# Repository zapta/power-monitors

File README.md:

POWER PLAY
==========

POWER PLAY are Arduino based smart power monitors that are used to measure and optimize the power consumption of battery operated devices such as smart phones. 

Following is a description of the POWER PLAY models.

POWER PLAY 3.8V
---------------

This model provides the most accurate results but requires modifying the tested device. The POWER PLAY 3.8V outputs regulated 3.8 volts are simulates the power provided by a single cell Li-Ion battery cell. It requires disconnecting the battery from the tested device and hooking the output of the POWER PLAY 3.8V instead.

This model has 1.3" OLED display and on board analysis firmware such that it can be operated standalone. In addition is has a FTDI/USB output port that can be used to log the raw data on an attached computer and use it latter for additional analysis.

POWER PLAY 3.8V
---------------

This model is identical to the POWER PLAY 3.8V except that it does not have the 3.8V regulator and instead it outputs a pass through 5V. It is intended to be used with unmodified test device by connecting the power to the charger input of the test device and measuring the current fluctuations after the internal battery is fully charged. This method provides less accurate results than the POWER PLAY 3.8V (with the battery removed) but is easier to use since it does not require modifying the test devices.

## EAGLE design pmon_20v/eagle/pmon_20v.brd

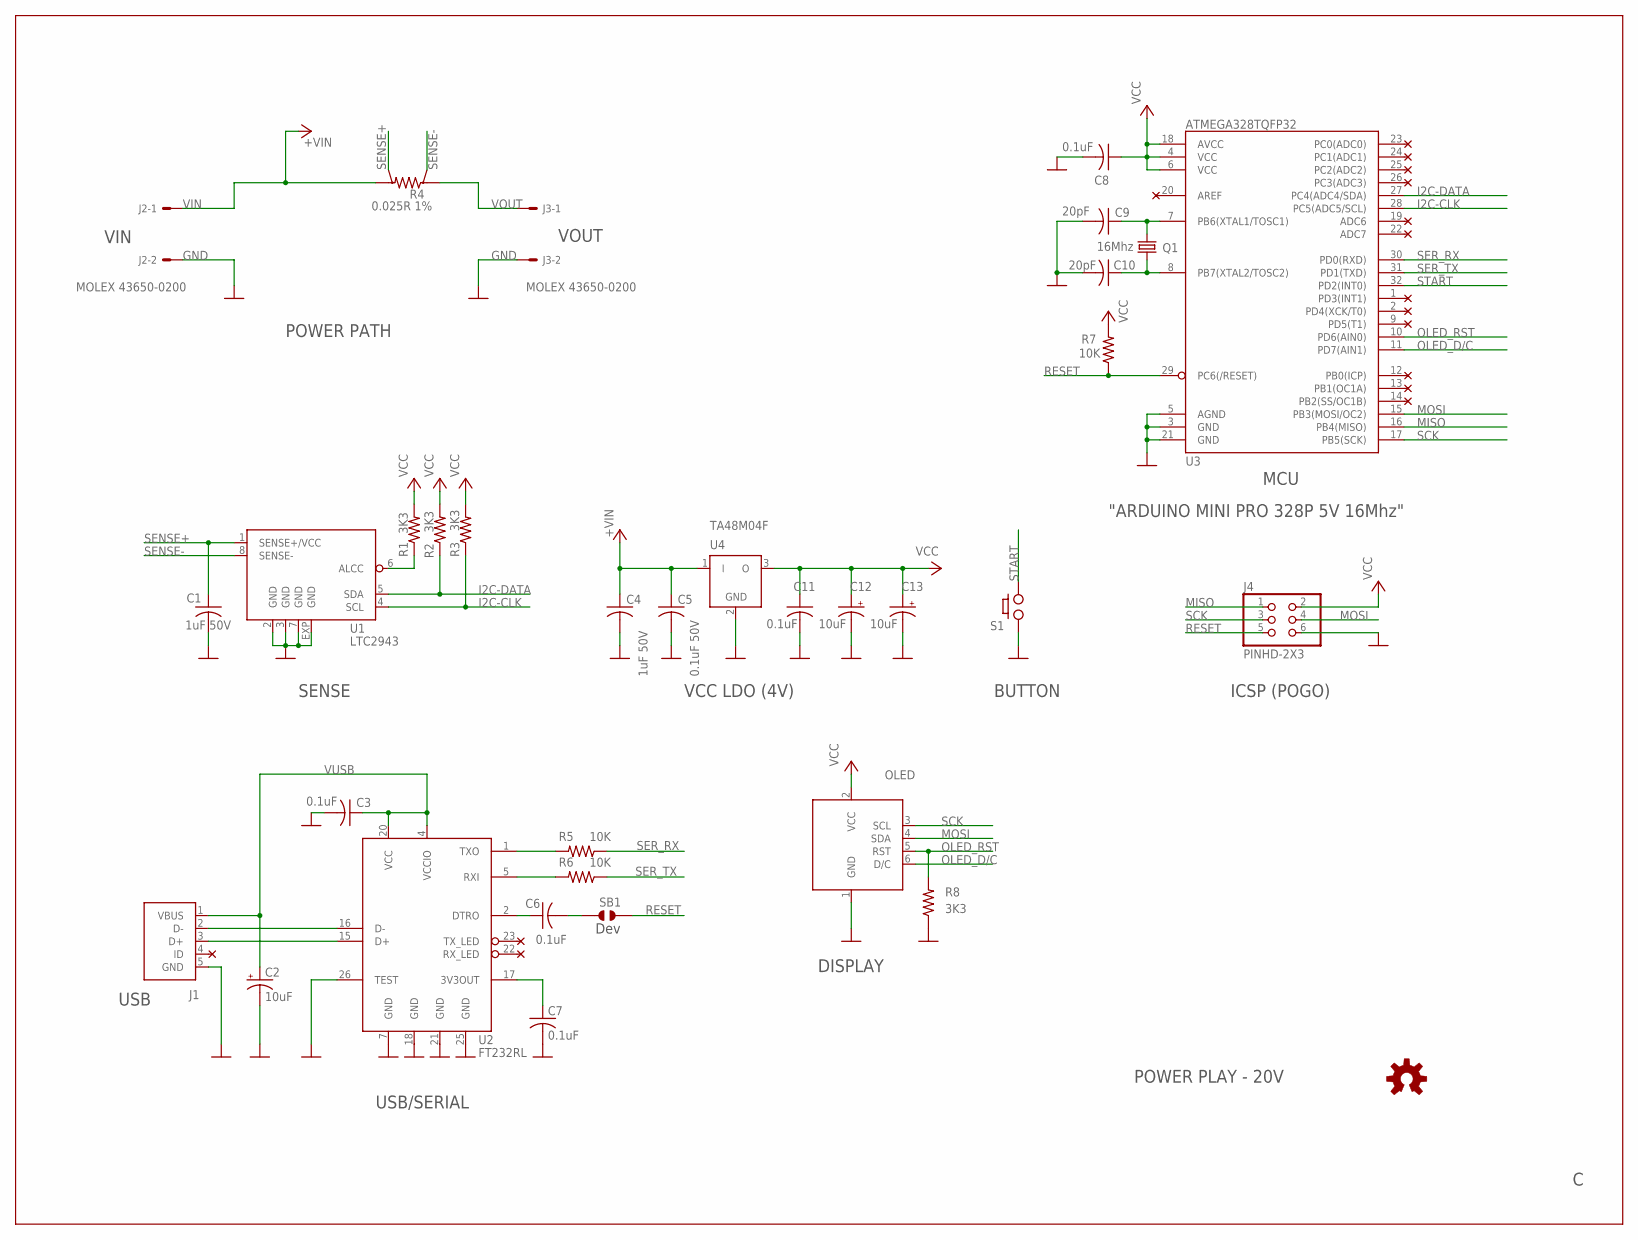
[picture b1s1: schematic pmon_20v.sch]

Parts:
C1, C4: 1uF 50V; C0603
C2, C12, C13: 10uF; A/3216-18R
C3, C6, C7, C8, C11: 0.1uF; C0603
C5: 0.1uF 50V; C0603
C9, C10: 20pF; C0603
J1: USB; USB-MICRO-ZX62RD-AB-5P8
J2, J3: MOLEX 43650-0200; POWER_CON
J4: PINHD-2X3; 2X03
OLED: OLED
Q1: 16Mhz; CRYSTAL-CTS406
R1, R2, R3, R8: 3K3; R0603
R4: 0.025R 1%; KELVIN-6432
R5, R6, R7: 10K; R0603
S1: PUSH_BUTTON; TLE1105
SB1: JUMPER_SOLDER_1X2
U1: LTC2943; DFN8-3X3
U2: FT232RL; SSOP28DB
U3: ATMEGA328TQFP32; TQFP32-08
U4: TA48M04F; DPACK
U$28: OSH

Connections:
GND: C1.2, C2.-, C3.2, C4.2, C5.2, C7.2, C8.2, C9.2, C10.2, C11.2, C12.-, C13.-, J1.5 (GND), J2.2, J3.2, J4.6, OLED.1 (GND), R8.1, S1.A (1), U1.2 (GND), U1.3 (GND), U1.7 (GND), U1.EXP (GND), U2.7 (GND), U2.18 (GND), U2.21 (GND), U2.25 (GND), U2.26 (TEST), U3.3 (GND), U3.5 (AGND), U3.21 (GND), U4.2 (GND)
I2C-CLK: R3.1, U1.4 (SCL), U3.28 (PC5(ADC5/SCL))
I2C-DATA: R2.1, U1.5 (SDA), U3.27 (PC4(ADC4/SDA))
MISO: J4.1, U3.16 (PB4(MISO))
MOSI: J4.4, OLED.4 (SDA), U3.15 (PB3(MOSI/OC2))
unnamed: R1.1, U1.6 (ALCC)
unnamed: C9.1, Q1.1, U3.7 (PB6(XTAL1/TOSC1))
unnamed: R5.2, U2.1 (TXO)
unnamed: C10.1, Q1.3 (2), U3.8 (PB7(XTAL2/TOSC2))
unnamed: R6.2, U2.5 (RXI)
unnamed: J1.3 (D+), U2.15 (D+)
unnamed: C6.1, U2.2 (DTRO)
unnamed: C6.2, SB1.1
unnamed: J1.2 (D-), U2.16 (D-)
unnamed: C7.1, U2.17 (3V3OUT)
OLED_D/C: OLED.6 (D/C), U3.11 (PD7(AIN1))
OLED_RST: OLED.5 (RST), R8.2, U3.10 (PD6(AIN0))
RESET: J4.5, R7.1, SB1.2, U3.29 (PC6(/RESET))
SCK: J4.3, OLED.3 (SCL), U3.17 (PB5(SCK))
SENSE+: C1.1, R4.V2, U1.1 (SENSE+/VCC)
SENSE-: R4.V1, U1.8 (SENSE-)
SER_RX: R5.1, U3.30 (PD0(RXD))
SER_TX: R6.1, U3.31 (PD1(TXD))
START: S1.B (2), U3.32 (PD2(INT0))
VCC: C8.1, C11.1, C12.+, C13.+, J4.2, OLED.2 (VCC), R1.2, R2.2, R3.2, R7.2, U3.4 (VCC), U3.6 (VCC), U3.18 (AVCC), U4.3 (O)
VIN: C4.1, C5.1, J2.1, R4.I2, U4.1 (I)
VOUT: J3.1, R4.I1
VUSB: C2.+, C3.1, J1.1 (VBUS), U2.4 (VCCIO), U2.20 (VCC)

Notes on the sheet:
USB/SERIAL
ICSP (POGO)
MCU
POWER PLAY - 20V
SENSE
POWER PATH
VIN
USB
VOUT
"ARDUINO MINI PRO 328P 5V 16Mhz"
BUTTON
DISPLAY
Dev
VCC LDO (4V)

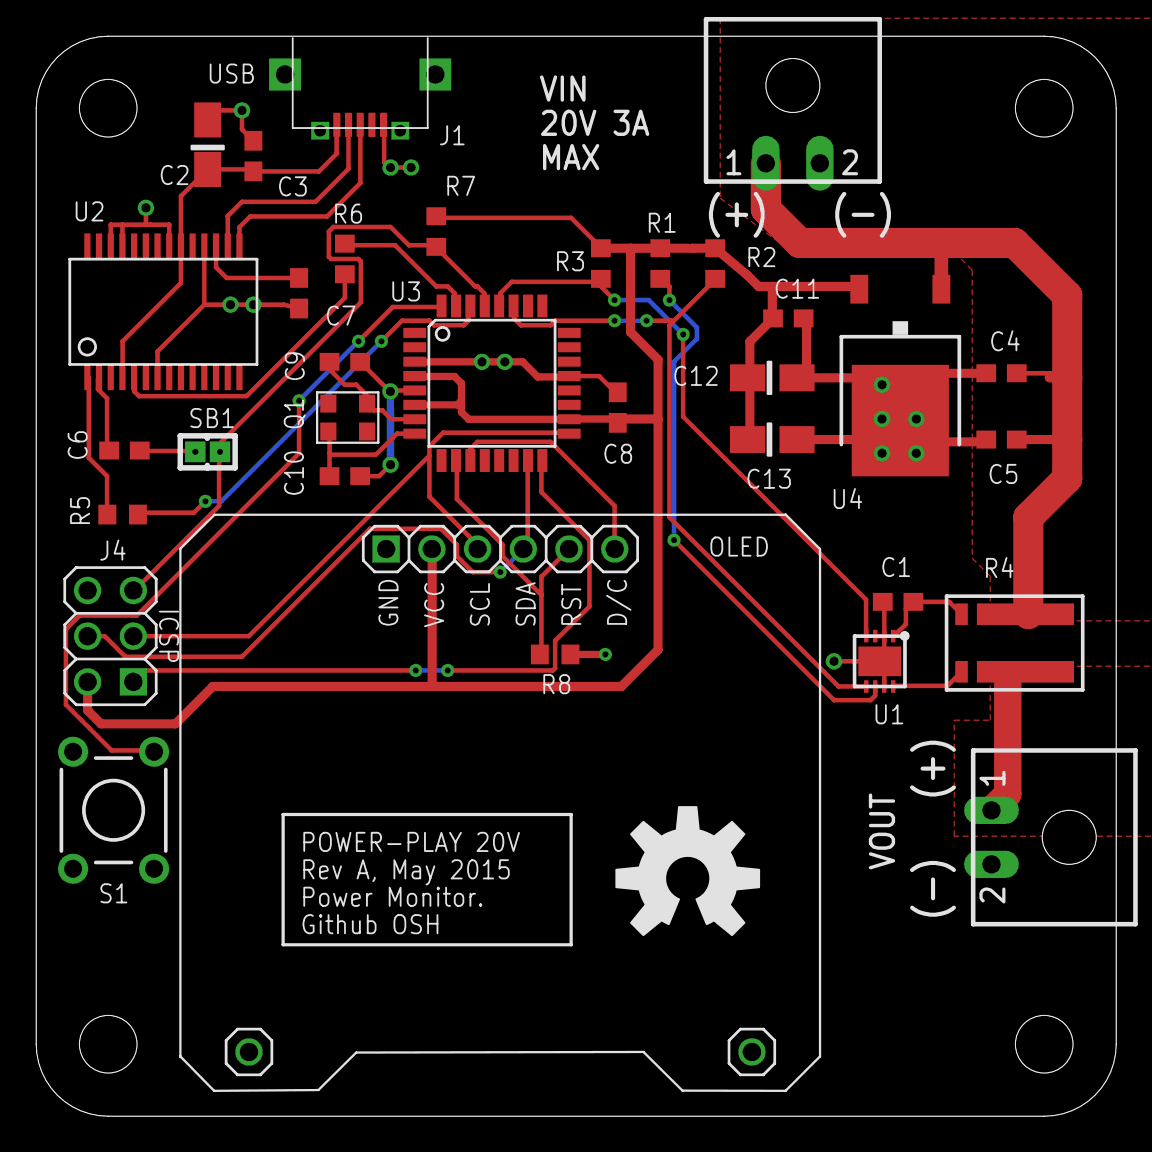
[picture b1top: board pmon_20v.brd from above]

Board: 2 copper layers, 60.0 x 60.0 mm, 34 parts (0 on the bottom side), 28 nets.

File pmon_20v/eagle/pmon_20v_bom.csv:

Quantity,Digi-Key Part Number,Description,Package,Manufacturer Name,Manufacturer Part Number,Part Numbers,Comments1,FC4L64R025FERCT-ND,0.025 ohm 1% 2W Kelvin,SMT 2512,Ohmite,FC4L64R025FER,R4,4,311-3.30KHRCT-ND,3.3K 5% 1/10W,SMT 0603,Yageo,RC0603JR-073K3L,R1  R2  R3  R8,Generic part3,311-10KGRCT-ND,10k 5% 1/10W,SMT 0603,Yageo,RC0603JR-0710KL,R5  R6  R7,Generic part2,311-1424-1-ND,20pF 50V 5%,SMT 0603,Yageo,CC0603JRNPO9BN200,C9  C10,Generic part5,311-1344-1-ND,0.1uf 10% 25V,SMT 0603,Yageo,CC0603KRX7R9BB104,C3  C5  C6  C8 C11,Generic part. May need to reduce C7 if interferes with ICSP reset (e.g. to 0.01)1,587-2400-1-ND,1uF 50V 10%,SMT 6030,Taiyo Uden,UMK107BJ105KA-T,C4,Generic part2,399-3684-1-ND,10uF 10%  16V,SMT 1206,Kemet,T491A106K010AT,C12  C13,Generic part1,CTX732CT-ND,16Mhz Crystal 20pf,4-SMD 3.20mm x 2.50mm,CTS-Frequency Control,403C11E16M00000,Q1,CTS 403 Series  20pF.1,ATMEGA328P-AURCT-ND,ATMEGA328P,TQFP32,Atmel,ATMEGA328P-AUR,U3,Atmel AVR328P1,768-1007-1-ND,FT232RL,SSOP28,FTDI,FT232RL-REEL,U2,1,LTC2943CDD#PBF-ND,LTC2943,DFN8,Liner Technology,LTC2943CDD#PBF,U1,Adjustable LDO 3A.1,TA48M04F(T6L1SNQ)CT-ND ,LDO 29V in 4V out,DPAK 2 + tab,Toshiba,"TA48M04F(T6L1,SNQ)",U4,Fixed LDO 4.0V. High input voltage1,P12197S-ND,Push button,,Panasonic Electronic Components,EVQ-PAG09K,S1,Panasonic EVQ-PAG09K2,S1011E-36-ND,"1 position  0.1""  straight",,Sullins Connector Solutions,PBC36SAAN,OLED mechanical support.,Generic part. Height above board should be at most 8.5mm. The part number here is for a 36 position breakable strip so it can be used for multiple boards.1,H11611CT-ND,Micro USB 'reversed' connector,,Hirose Electric Co Ltd,ZX62RD-AB-5P8,J1,Hirose ZX62RD-AB-5P8.  Make sure it is a 'reversed' connector  otherwise the signals will be in reversed order.2,WM1860-ND,PCB conn 2wire right angle,,Molex Inc,436500200,J2  J3,2,WM1845-ND,Conn header 2 wire,,Molex Inc,436450200,,4,WM2776CT-ND,Conn header contact female,,Molex Inc,430300003,,4,335-1156-ND,M3x6mm  pan head  philips machine screw,,APM Hexseal,RM3X6MM 2701,,Top cover screws4,335-1148-ND,M3x10mm  pan head  philips machine screw,,APM Hexseal,RM3X10MM 2701,,Bottom cover screws4,952-1515-ND,M3x6mm  round  threaded  female/female metal standoff,,Harwin,R30-5000602,,Top cover standoff4,952-1526-ND,M3x3mm round  non threaded nylon or metal spacer,,Harwin,R30-6700394,,Bottom cover spacer1,N/A,"Heltec 1.3"" SPI 128X64 OLED WHITE monochrome display with RST pin.",,Heltec,,OLED,Must have SSD1306 controller and these 6 pins: GND  VCC  SCL  SDA  RST  D/C (picture here  http://i.imgur.com/y3cWazS.jpg).  Manufacturer is http://www.heltec.cn. Heltec also similar blue models (with sh1063 controller) and 'new' models with different 6 pins (VCC and GND swapped  no RST pin)  these two models are incompatible with the current POWER PLAY design.1,N/A,PCB,,,,,Order the PCB from your favorite PCB manufacturer (2 layers  60x60mm).  Make sure to order a SMD stencil  preferably 5mil stainless steal but even a 5 mil stencil from oshstencils.com should work.1,N/A,Top cover,,,,,"Laser cut fluorescent green 1/8"" acryilic."1,N/A,Bottom Cover,,,,,"Laser cut fluorescent green 1/8"" acryilic."

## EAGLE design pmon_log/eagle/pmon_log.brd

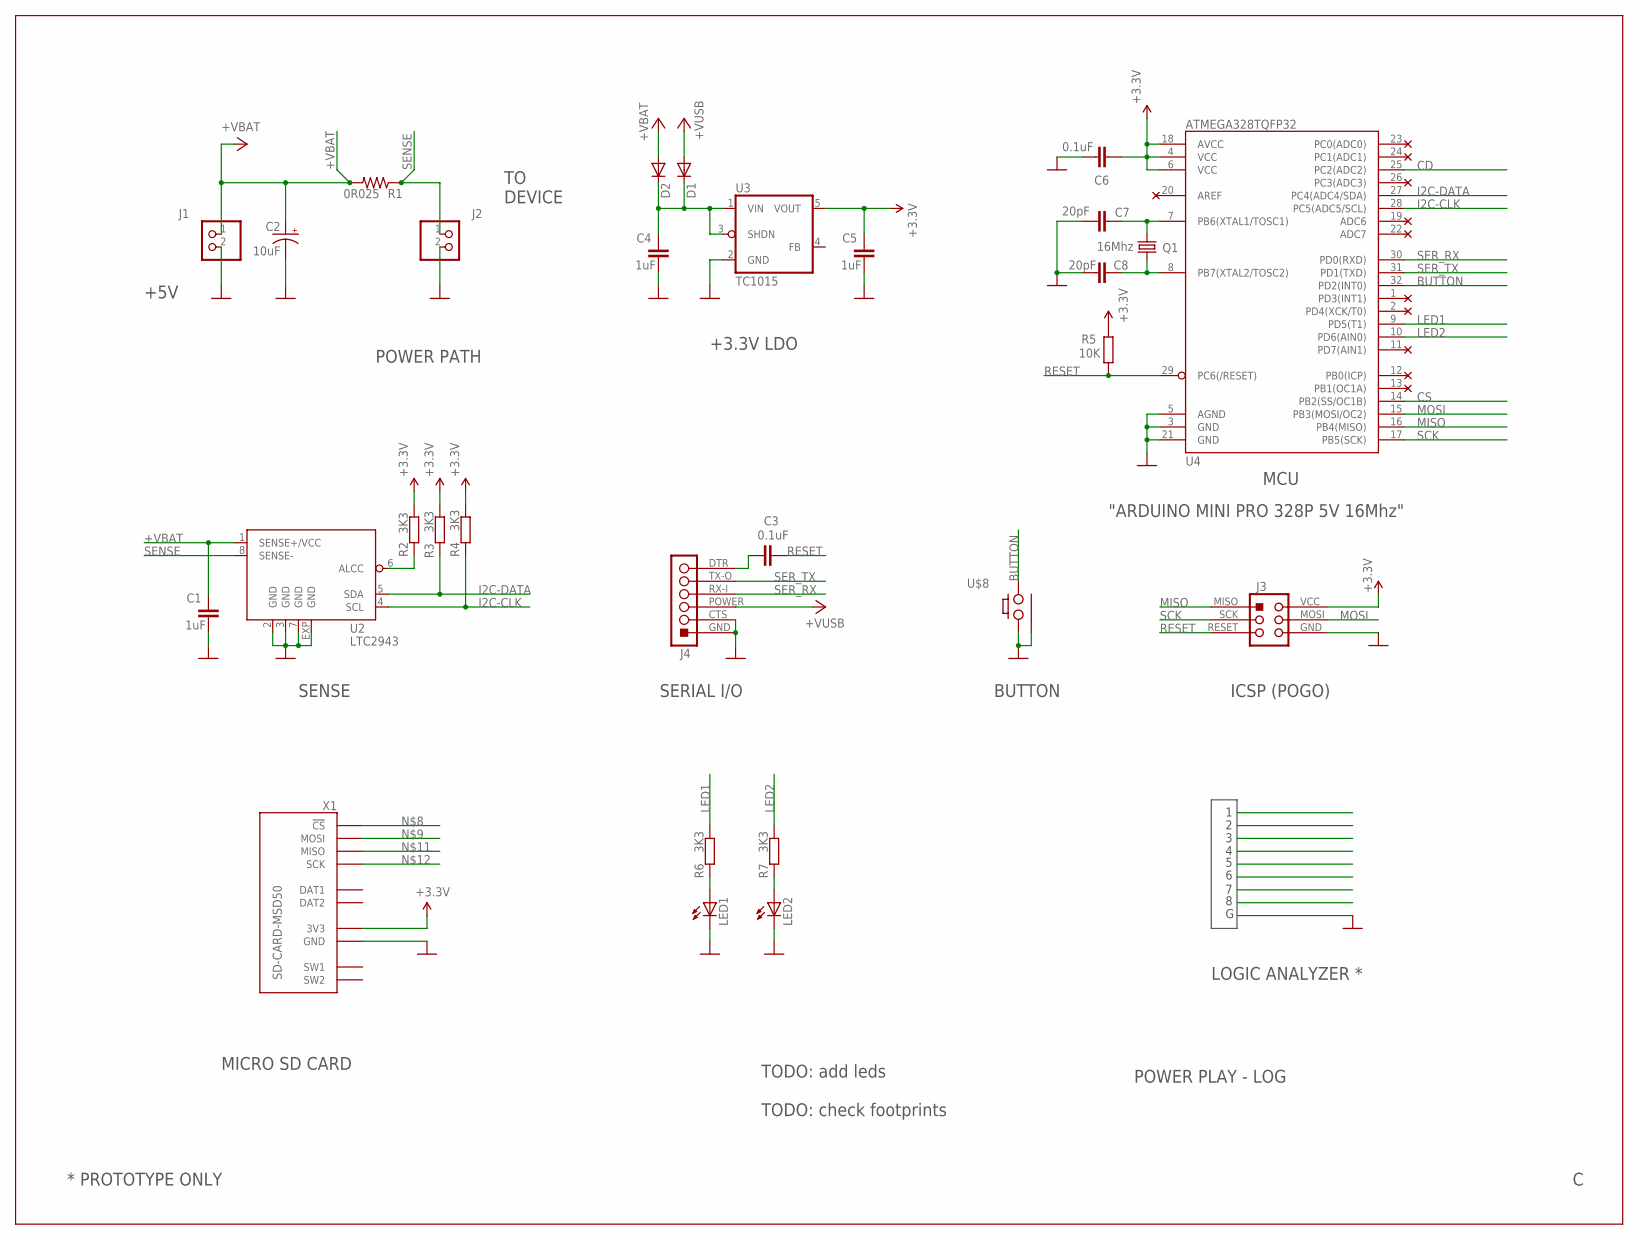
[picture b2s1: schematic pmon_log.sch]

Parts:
C1, C4, C5: 1uF; C0402K
C2: 10uF; A/3216-18R
C3, C6: 0.1uF; C0402K
C7, C8: 20pF; C0402K
D1, D2: DIODE-SC79_INFINEON; SC79_INFINEON
J1, J2: PINHD-1X2; 1X02
J3: ICSP
J4: SERIAL_HEADER
LED1, LED2: LEDCHIPLED_0603; CHIPLED_0603
Q1: 16Mhz; CRYSTAL-CTS406
R1: 0R025; R0603
R2, R3, R4, R6, R7: 3K3; R0402
R5: 10K; R0402
U2: LTC2943; DFN8-3X3
U3: TC1015; SOT25
U4: ATMEGA328TQFP32; TQFP32-08
U$8: PUSH_BUTTON_GND
X1: SD-CARD-MSD50; SD_5031821853

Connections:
+3.3V: X1.VCC (3V3)
+4V: C5.1, C6.1, J3.VCC, R2.2, R3.2, R4.2, R5.2, U3.5 (VOUT), U4.4 (VCC), U4.6 (VCC), U4.18 (AVCC)
+USB: D1.A, J4.POWER (3)
+VBAT: C1.1, C2.+, D2.A, J1.1, R1.2, U2.1 (SENSE+/VCC)
BUTTON: U4.32 (PD2(INT0)), U$8.HOLE1 (2)
CD: U4.25 (PC2(ADC2))
CS: U4.14 (PB2(SS/OC1B))
GND: C1.2, C2.-, C4.2, C5.2, C6.2, C7.2, C8.2, J1.2, J2.2, J3.GND, J4.CTS (2), J4.GND (1), LED1.C, LED2.C, U2.2 (GND), U2.3 (GND), U2.7 (GND), U2.EXP (GND), U3.2 (GND), U4.3 (GND), U4.5 (AGND), U4.21 (GND), U$8.A1 (1), U$8.GND, X1.GND
I2C-CLK: R4.1, U2.4 (SCL), U4.28 (PC5(ADC5/SCL))
I2C-DATA: R3.1, U2.5 (SDA), U4.27 (PC4(ADC4/SDA))
LED1: R6.2, U4.9 (PD5(T1))
LED2: R7.2, U4.10 (PD6(AIN0))
MISO: J3.MISO, U4.16 (PB4(MISO))
MOSI: J3.MOSI, U4.15 (PB3(MOSI/OC2))
unnamed: R2.1, U2.6 (ALCC)
unnamed: C7.1, Q1.1, U4.7 (PB6(XTAL1/TOSC1))
unnamed: C4.1, D1.C, D2.C, U3.1 (VIN), U3.3 (SHDN)
unnamed: LED1.A, R6.1
unnamed: LED2.A, R7.1
unnamed: C8.1, Q1.3 (2), U4.8 (PB7(XTAL2/TOSC2))
unnamed: C3.2, J4.DTR (6)
RESET: C3.1, J3.RESET, R5.1, U4.29 (PC6(/RESET))
SCK: J3.SCK, U4.17 (PB5(SCK))
SENSE: J2.1, R1.1, U2.8 (SENSE-)
SER_RX: J4.RX-I (4), U4.30 (PD0(RXD))
SER_TX: J4.TX-O (5), U4.31 (PD1(TXD))

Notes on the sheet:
ICSP (POGO)
MCU
POWER PLAY - LOG
SENSE
POWER PATH
+5V
LOGIC ANALYZER *
TO DEVICE
* PROTOTYPE ONLY
"ARDUINO MINI PRO 328P 5V 16Mhz"
BUTTON
+3.3V LDO
TODO: add leds
TODO: check footprints
SERIAL I/O
MICRO SD CARD

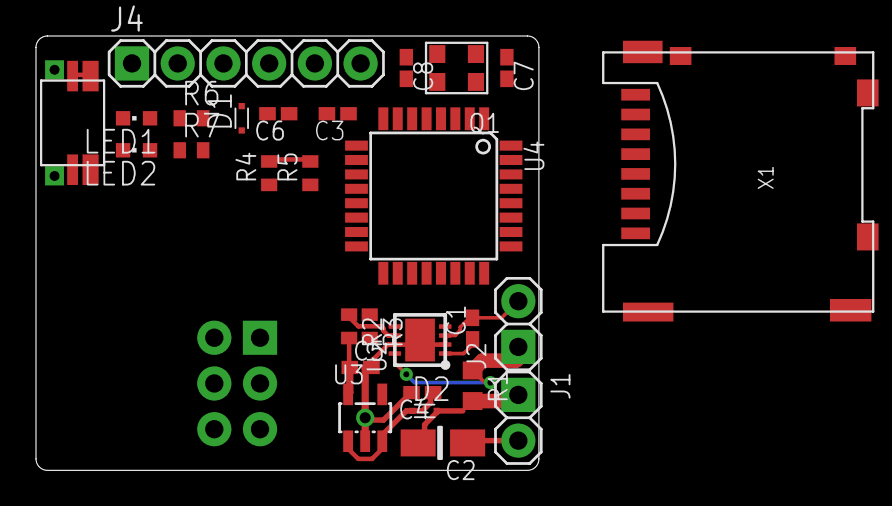
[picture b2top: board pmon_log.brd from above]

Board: 2 copper layers, 27.9 x 24.1 mm, 29 parts (1 on the bottom side), 23 nets.

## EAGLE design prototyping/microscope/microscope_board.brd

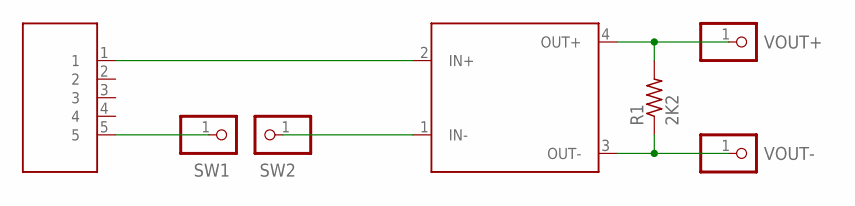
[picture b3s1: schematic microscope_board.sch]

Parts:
R1: 2K2; R0805
SW1, SW2: PINHD-1X1; 1X01
U$1: DC_DC
U$2: USB_CONNECTOR
VOUT+: PINHD-1X1; 1X01
VOUT-: PINHD-1X1; 1X01

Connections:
unnamed: R1.2, U$1.4 (OUT+), VOUT+.1
unnamed: R1.1, U$1.3 (OUT-), VOUT-.1
unnamed: U$1.2 (IN+), U$2.1
unnamed: SW1.1, U$2.5
unnamed: SW2.1, U$1.1 (IN-)

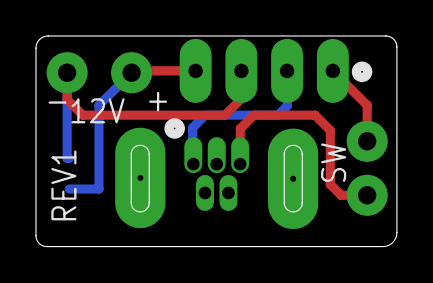
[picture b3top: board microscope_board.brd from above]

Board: 2 copper layers, 20.1 x 11.7 mm, 7 parts (1 on the bottom side), 5 nets.

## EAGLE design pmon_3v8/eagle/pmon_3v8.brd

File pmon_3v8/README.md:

POWER PLAY 3.8V
===============

## OVERVIEW
POWER PLAY 3V8 is an Arduino based measurement tool that is used to measure the power consumption of mobile devices under different conditions and software versions. It provides 3.8V 2A DC power that simulates a single cell Li-ion battery and is connected to the device **instead of the battery**. The POWER PLAY 3V8 analyzes the current pattern consumed by the device and provides aggregated data on an integral a 1.3" OLED display. It also output the data to a USB/Serial port so it can be logged by a computer for further analysis. The computer based logging is optional and in most cases not consumed since the POWER PLAY 3V8 provides the key results on the display in real time (e.g. the average current consumption over the measurement period).

**WARNING using the POWER PLAY 3.8V required modified devices with batteries removed. This modification should be done by qualified persons only due to the risk of fire, personal injury and even death. The POWER PLAY 3V8 information is provided here as-is and you must consult a qualified person before using it in any way. NEVER operate the POWER PLAY 3V8 with the battery connected to the device under test.**

1. +5V power input micro USB connector. This connector should be connected to a standard 5V charger and is used to power the POWER PLAY 3V8 and the device under test. It is important to use a charger that can provide sufficient current even during peak current consumption by the device under test. When testing a typical smart phone, powering the POWER PLAY 3V8 from a USB port or a small 1A charger typically result in insufficient current and unstable operation.

2. Power output connection to the device. This is a 3 pin standard servo connector (JR and Hitec style) with ground at the center pin and 3.8V DC (typical) at the two end pins (it's sufficient to use only one of them). This output voltage is adjustable (see below) and is connected to the device instead of the battery, emulating a single cell Lithium-ion battery.

3. USB connector. Using this connector is optional. It allows to log the raw data on an attached computer for later analysis. This connector implements a FTDI serial over USB port and can be access as a serial port on standard Mac OSX, Linux and Windows computers without additional drivers. The emulated serial port is 115.2kbs, 8 data bit, no parity and the data is in ASCII text format.

4. Display. This is a 1.3" monochrome OLED display that shows the analysis results. The display supports multiple pages with different data items.

5. Operation button. A short click switch the displayed data page and a long press (~4 seconds) resets the analysis variables and starts a new analysis session. Holding this button pressed while powering the POWER PLAY 3V8 activates the test screen (for post manufacturing tests).

6. This is a multi turn trim potentiometer that allows to adjust the output voltage in the range 3.6V - 4.2V. It is accessible from the side of the POWER PLAY 3V8 and requires a small flat screwdriver.

7. Auto Reset. This is a solder jumper on the PCB that controls the the USB auto reset feature. When shorted, establishing a new connection via the USB connector resets the POWER PLAY 3V8. This is useful when developing firmware for the POWER PLAY 3V8 using the Arduino IDE. If the auto reset is not desired (e.g. in order to have analysis sessions non interrupted by connecting the USB port), the short should be disconnected with a solder iron (after removing the 4 top screws and top cover).

TODO: add an overall picture with annotation for connectors, display, button and trim pot.

## FUNCTIONAL BLOCK DIAGRAM

* **Voltage regulator** - a 5V to 3.8v low dropout (LDO) voltage regulator. The output voltage (nominal 3.8V) can be set by the small multi turn potentiometer on the right hand of the device.
* **Shunt resistor** - this is a small (25 milliohms) 1% Kelvin resistor that is used to sample the current consumed the the device. The voltage drop on the shunt does not affect the output voltage of the POWER PLAY 3V8 because of the feedback loop between the output voltage and the LDO.
* **Coulomb counter** - this is an analog circuit that continuously integrate the current through the shunt resistor and generates a pulse ('tick') whenever the charge since the last tick reaches a predefined value. (charge is the integral of current over time and is measured in Ampere Hours). For more information read the LTC2943 datasheet at http://www.linear.com/product/LTC2943.
* **Charge counter** - this is a digital counter that counts the Coulomb counter ticks. It provides the long term current integration.
* **Analysis** - this is firmware that tracks the current patterns and computes real time summary data such as momentary current, accumulated charge, number of times device transitioned from standby to wake mode and so on.
* **Display** - a small 1.3" OLED display that display the analysis results. The display has several pages, each with different data items, that can be switched using the button.
* **Computer** - this is an optional computer that logs the data over a USB connection. In most cases, the results displayed on the OLED displayed are sufficient and the computer is not necessary. 

## CONNECTION DIAGRAM

Plug the +5V micro usb connector to a USB charger with sufficient current (e.g. 2A). Plug the modified device to the DEVICE connector. Optional: to log the data on a computer connect the USB port to a computer and run a logging program or script (the POWER PLAY 3V8 looks like a 115.2kbs FTDI serial over USB port).

## ANALYSIS

The POWER PLAY 3V8 performs the analysis by dividing the time into slots of 100ms each (10Hz). For each time slot the analysis firmware samples the number of charge ticks occurred in that time slot (partial ticks are rolled to the next time slots, avoiding integration errors) and tracks the total ticks and time in global analysis counters. These counters are reset when the analysis is reset by long pressing the button. These values are used to compute, report and display the following values among others:

* Charge in last time slot.
* Average current during last time slot.
* Last time slot classification (I < ~80ma ? 'standby' : 'wake').
* Total analysis time.
* Total analysis charge (AmpHour).
* Average current during the analysis period.
* Total times of 'wake' and 'standby' slots.
* Total charge in 'wake' and 'standby' slots.
* Number of transitions from a 'standby' to 'wake' time slot.

The most important value from the above list is the average current during the analysis since it is inversely proportional to the expected battery life (for a given battery capacity).

Note: the analysis also samples and reports the momentary voltage level at each slot but in general it assumes that the voltage is fixed and thus does not track power (Watt) or energy (Watt Hour).

## OPERATION

Operating the POWER PLAY 3V8 is very simple. Connect the POWER PLAY 3V8 to a 5V 2A charger and the device under test as described above, reset the analysis by long pressing the button (~4 seconds) and let the device operate under the desired conditions. The analysis is done is real time and the results are shown on the display. Click the button to switch between display pages to see the desired values. 

IMPORTANT: the charger must be able to provide the peak current of the device under test. Make sure to have a brand name charger with sufficient power capabilities (e.g. 2A or larger). If the charger cannot provides the peak current, the device will turn off occasionally. 

## LOG FORMAT
POWER PLAY output raw data for logging and offline analysis via the USB port. When connecting to a Linux, Mac OSC or Windows 
computer, the POWER PLAY appears as a serial port without having to install any special driver (it uses the default FTDI driver).
The serial port parameters are 115,200 bps, 8 data bit, no parity and it provides text based data (with CR/LF line ending)
with one record every 100 milliseconds. Each record contains the values listed below with a single space separator between
them.

```
8.200 0.131 0.000 0.163 0 8200 1 1
8.300 0.155 0.000 0.163 0 8300 1 1
8.400 0.131 0.000 0.163 0 8400 1 1
8.500 0.042 0.000 0.161 100 8400 1 0
8.600 0.018 0.000 0.159 200 8400 1 0
8.700 0.018 0.000 0.158 300 8400 1 0
8.800 0.012 0.000 0.156 400 8400 1 0
8.900 0.018 0.000 0.155 500 8400 1 0
9.000 0.030 0.000 0.153 600 8400 1 0
9.100 0.060 0.000 0.152 600 8500 2 1
9.200 0.042 0.000 0.151 700 8500 2 0
```

The fields of each log line are as follows

* **T** - Timestamp since the beginning of the analysis (long press the button) in milliseconds.
* **I** - Average current during the last 100ms time slot, in Amperes.
* **Q** - Total charge since the beginning of the analysis in Ampere/Hours.
* **Iavg** - Average current since the beginning of the analysis in millliamps.
* **Ts** - Total time since the beginning of the analysis of 100ms time slot that were classified as 'standby' (average current was lower than a predefined threshold.
* **Tw** - Total time since the beginning of the analysis of 100ms time slot that were classified as 'wake' (average current was higher than a predefined threshold. (this field is redundant since it is always equals T - Ts).
* **Nw** - number of transitions from a 'standby' (100ms) time slot to a 'wake' time slot. 
* **W** - a boolean flag that indicates if the last 100ms time slot was classified as 'wake' (value = 1) or as 'standby' (value = 0).

## INSTRUMENTING A DEVICE
The process of instrumenting a mobile device to be used with POWER PLAY 3.8V varies for each device and should be done only by qualified personal that understand the device and the hazards of dealing with rechargeable Li-Ion batteries (risk or fire, personal injury and death so **beware**). For that reason, it is in out of the scope of this document.

Following are the steps used to instrument one specific phone model (Nexus 5) that was used to test the POWER PLAY 3.8V. This is provided as general information only and not as a comprehensive guide. The procedure for other devices can be very different, some may require additional capacitors in parallel to the two wires, other can require special 'fake' batteries while others can be completely incompatible with POWER PLAY 3.8V.

1. Open the back cover (pry around)
2. Remove the black plastic cover above the battery (require removal of 6 small screws).
3. Carefully disconnect the battery connector and the large flex connector next to it.
4. Remove the battery (you need to pry below it, be careful not to damage the battery).
5. Place back the large flex cable.
6. Solder two wires to the points shown the in the picture below.
7. Put back the black cover and secure with the 6 screws.
8. Cut a small notch at the edge of the back cover to have clearance for the two wires.
9. Put back the black cover.
10. Solder the two wires to a 3 position HiTech/JR (but not Futaba) servo connector. Connect the center position to the (-) wires and one of the end positions to the (+) wire.

The Nexus 5 with cover and battery removed and two wires soldered.

A close up of the two connection points.

The phone with the black cover back in place and the wires secured with tape.

The exit point of the two wires.

## FIRMWARE DEVELOPMENT

POWER PLAY 3.8V is compatible with the Arduino IDE and its firmware is an Arduino sketch whose source code is available in this directory. Here are a few notes that will help you setup the development environment.

* You need to power the POWER PLAY 3.8V via its +5V connector in addition to connecting the USB port to the host computer with the Arduino IDE.
* The POWER PLAY 3.8V looks to the Arduino IDE as an Arduino Pro Mini 16Mhz 5V ATMEGA328 board. You need to select it in the Tool section of the IDE menu.
* You can use the IDE serial monitor facility to view output from the POWER PLAY 3.8V.
* The POWER PLAY 3.8V sketch uses the U8glib graphic library. You need to install it on your Arduino IDE before being to compile the POWER PLAY 3.8V sketch. To do so, follow the 'manual instructions' here https://code.google.com/p/u8glib/wiki/u8glib (using the IDE's library import function results in compilation errors).

## BUILDING POWER PLAY 3V8

Follow these steps to build your own POWER PLAY: 

* Purchase the electronic components listed in the Bill Of Material (BOM) file. Most components are available from common sources such as digikey.com. You can purchase the OLED display directly from heltec.cn or from retailers such as eBay sellers. Make sure to purchase a white SPI display with 6 pins that match the pins in the schema (these display use the SSD1306 controller).
* Order the printed circuit board (PCB). It is a 2 layers PCB with a Sick of Beige 60mm x 60mm form factor. Some vendors such as OSHPark.com accept Eagle .brd files directly. Others such as elecrow.com require you to generate gerber files using their custom Eagle .cam files.
* Order a SMD stencil (5mil or 0.125mm) for the PCB. For best results, use a metal stencil (e.g. from elecrow.com) rather than mylar.
(optional) Make the top and bottom laser cut covers. We got the best results with acrylic 1/8” fluoro blue or green. If you do not have access to a laser cutter, you can order online from services such as ponoko.com. 
* Print, pick-and-place and reflow the SMD components, including the two micro USB connectors (use solder paste, the stencil and the reflow method of your choice such as hot air station, hot plate or a toaster oven).
* Solder the through-hole components (two 1 pin OLED support posts, OLED display, push button, and 3 pin output header). Connecting the solder jumper SB1 is optional but recommended.
* Power the board via the +5V connector and use an ICSP programmer of your choice (e.g. Atmel ICSP MKII with pogo pins) to program the MCU  (see the script file icsp_program_all.sh for an example). Alternatively, you can program the MCU before soldering, using a universal programmer. This step programs the MCU fuses, the MCU Arduino bootloader, and the POWER PLAY firmware. 
* (optional) Assemble the top and bottom covers using the screws and spacers listed in the BOM. If not using the covers, you can use screws and nuts to have the PCB standing on 4 legs.

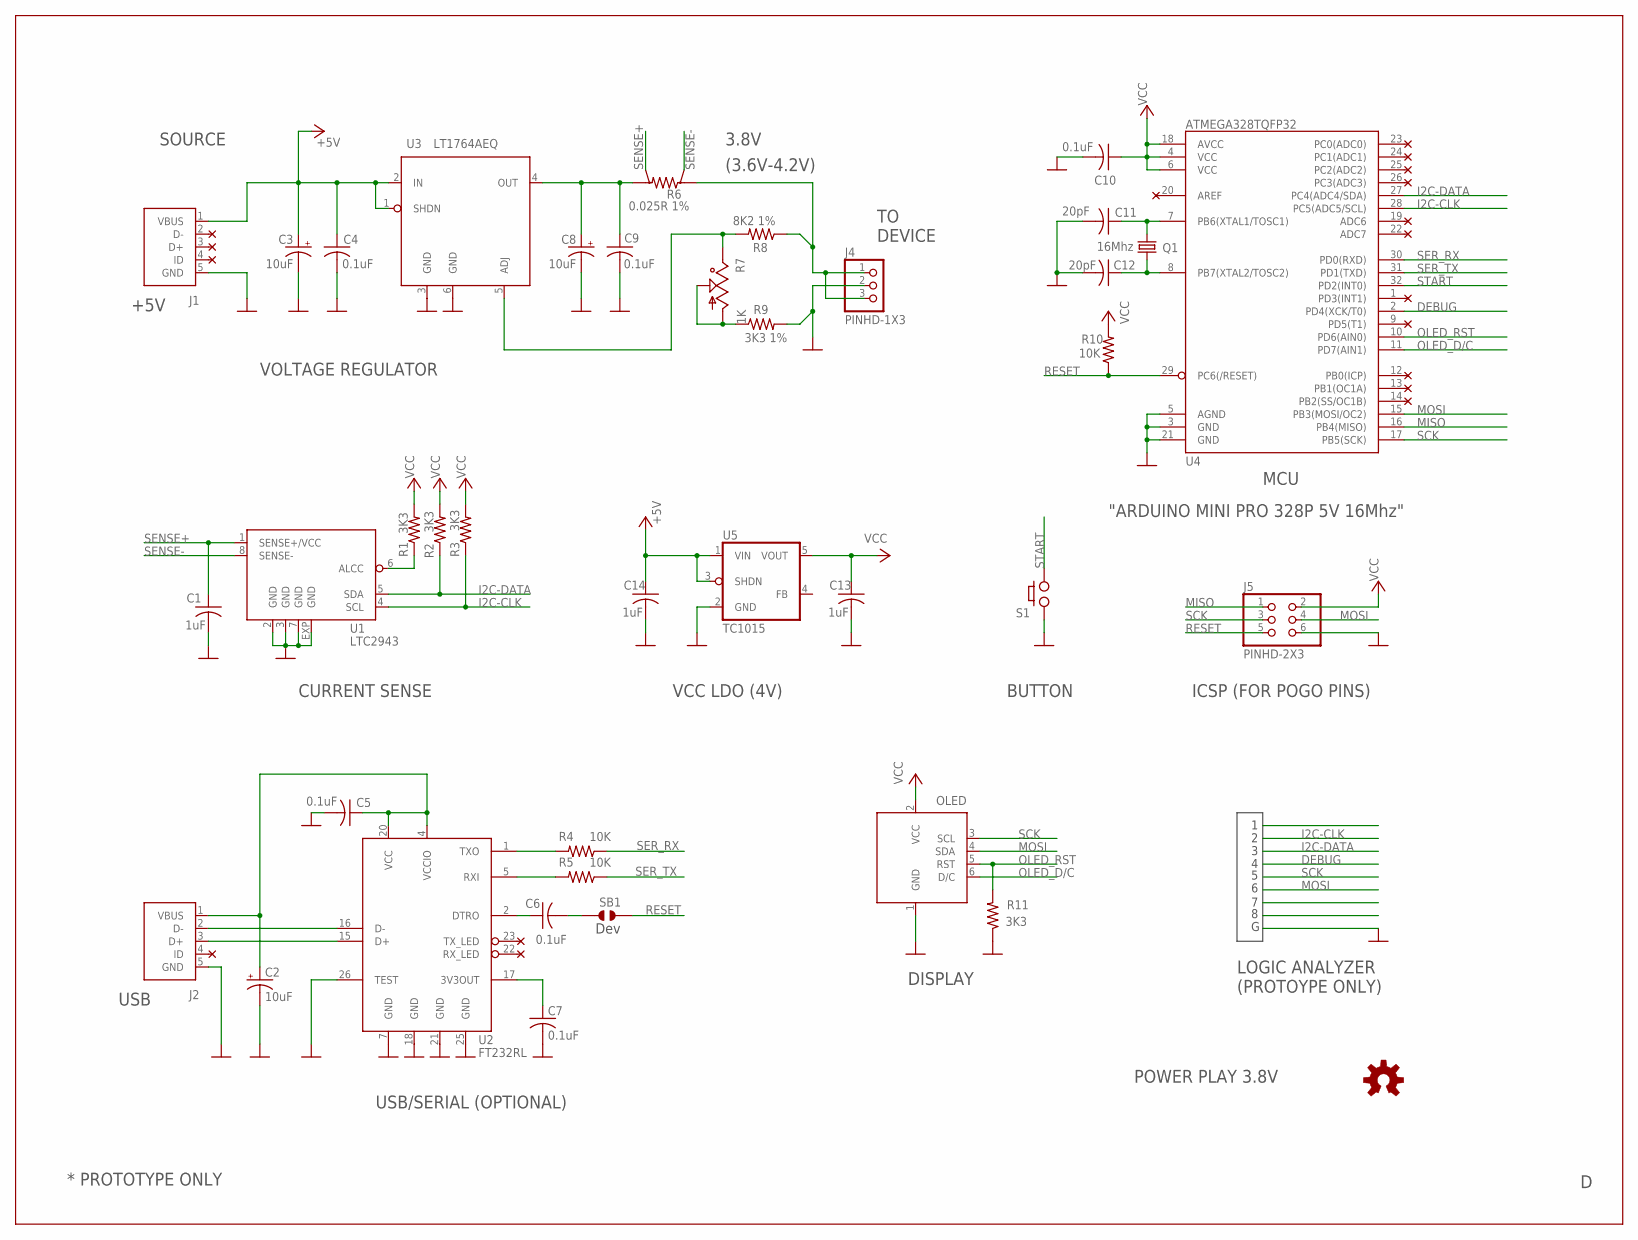
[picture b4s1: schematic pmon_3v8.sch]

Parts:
C1, C13, C14: 1uF; C0603
C2, C3, C8: 10uF; A/3216-18R
C4, C5, C6, C7, C9, C10: 0.1uF; C0603
C11, C12: 20pF; C0603
J1, J2: USB; USB-MICRO-ZX62RD-AB-5P8
J4: PINHD-1X3; 1X03
J5: PINHD-2X3; 2X03
OLED: OLED
Q1: 16Mhz; CRYSTAL-CTS406
R1, R2, R3, R11: 3K3; R0603
R4, R5, R10: 10K; R0603
R6: 0.025R 1%; KELVIN-6432
R7: 1K; TRIM-POT_SM-42/43A
R8: 8K2 1%; R0603
R9: 3K3 1%; R0603
S1: PUSH_BUTTON; TLE1105
SB1: JUMPER_SOLDER_1X2
U1: LTC2943; DFN8-3X3
U2: FT232RL; SSOP28DB
U3: LT1764AEQ; TO263-5
U4: ATMEGA328TQFP32; TQFP32-08
U5: TC1015; SOT25
U$28: OSH

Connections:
+5V: C3.+, C4.1, C14.1, J1.1 (VBUS), U3.1 (SHDN), U3.2 (IN), U5.1 (VIN), U5.3 (SHDN)
DEBUG: U4.2 (PD4(XCK/T0))
GND: C1.2, C2.-, C3.-, C4.2, C5.2, C7.2, C8.-, C9.2, C10.2, C11.2, C12.2, C13.2, C14.2, J1.5 (GND), J2.5 (GND), J4.2, J5.6, OLED.1 (GND), R9.2, R11.1, S1.A (1), U1.2 (GND), U1.3 (GND), U1.7 (GND), U1.EXP (GND), U2.7 (GND), U2.18 (GND), U2.21 (GND), U2.25 (GND), U2.26 (TEST), U3.3 (GND), U3.6 (GND), U4.3 (GND), U4.5 (AGND), U4.21 (GND), U5.2 (GND)
I2C-CLK: R3.1, U1.4 (SCL), U4.28 (PC5(ADC5/SCL))
I2C-DATA: R2.1, U1.5 (SDA), U4.27 (PC4(ADC4/SDA))
MISO: J5.1, U4.16 (PB4(MISO))
MOSI: J5.4, OLED.4 (SDA), U4.15 (PB3(MOSI/OC2))
unnamed: R1.1, U1.6 (ALCC)
unnamed: C11.1, Q1.1, U4.7 (PB6(XTAL1/TOSC1))
unnamed: R4.2, U2.1 (TXO)
unnamed: C12.1, Q1.3 (2), U4.8 (PB7(XTAL2/TOSC2))
unnamed: R5.2, U2.5 (RXI)
unnamed: C8.+, C9.1, R6.I2, U3.4 (OUT)
unnamed: J2.3 (D+), U2.15 (D+)
unnamed: C6.1, U2.2 (DTRO)
unnamed: C6.2, SB1.1
unnamed: J2.2 (D-), U2.16 (D-)
unnamed: C7.1, U2.17 (3V3OUT)
unnamed: R7.1, R7.2, R9.1
unnamed: R7.3, R8.2, U3.5 (ADJ)
unnamed: J4.1, J4.3, R6.I1, R8.1
OLED_D/C: OLED.6 (D/C), U4.11 (PD7(AIN1))
OLED_RST: OLED.5 (RST), R11.2, U4.10 (PD6(AIN0))
RESET: J5.5, R10.1, SB1.2, U4.29 (PC6(/RESET))
SCK: J5.3, OLED.3 (SCL), U4.17 (PB5(SCK))
SENSE+: C1.1, R6.V2, U1.1 (SENSE+/VCC)
SENSE-: R6.V1, U1.8 (SENSE-)
SER_RX: R4.1, U4.30 (PD0(RXD))
SER_TX: R5.1, U4.31 (PD1(TXD))
START: S1.B (2), U4.32 (PD2(INT0))
VCC: C10.1, C13.1, J5.2, OLED.2 (VCC), R1.2, R2.2, R3.2, R10.2, U4.4 (VCC), U4.6 (VCC), U4.18 (AVCC), U5.5 (VOUT)
VUSB: C2.+, C5.1, J2.1 (VBUS), U2.4 (VCCIO), U2.20 (VCC)

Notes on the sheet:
USB/SERIAL (OPTIONAL)
ICSP (FOR POGO PINS)
MCU
POWER PLAY 3.8V
CURRENT SENSE
VOLTAGE REGULATOR
+5V
LOGIC ANALYZER (PROTOYPE ONLY)
USB
TO DEVICE
3.8V
* PROTOTYPE ONLY
"ARDUINO MINI PRO 328P 5V 16Mhz"
BUTTON
SOURCE
DISPLAY
Dev
VCC LDO (4V)
(3.6V-4.2V)

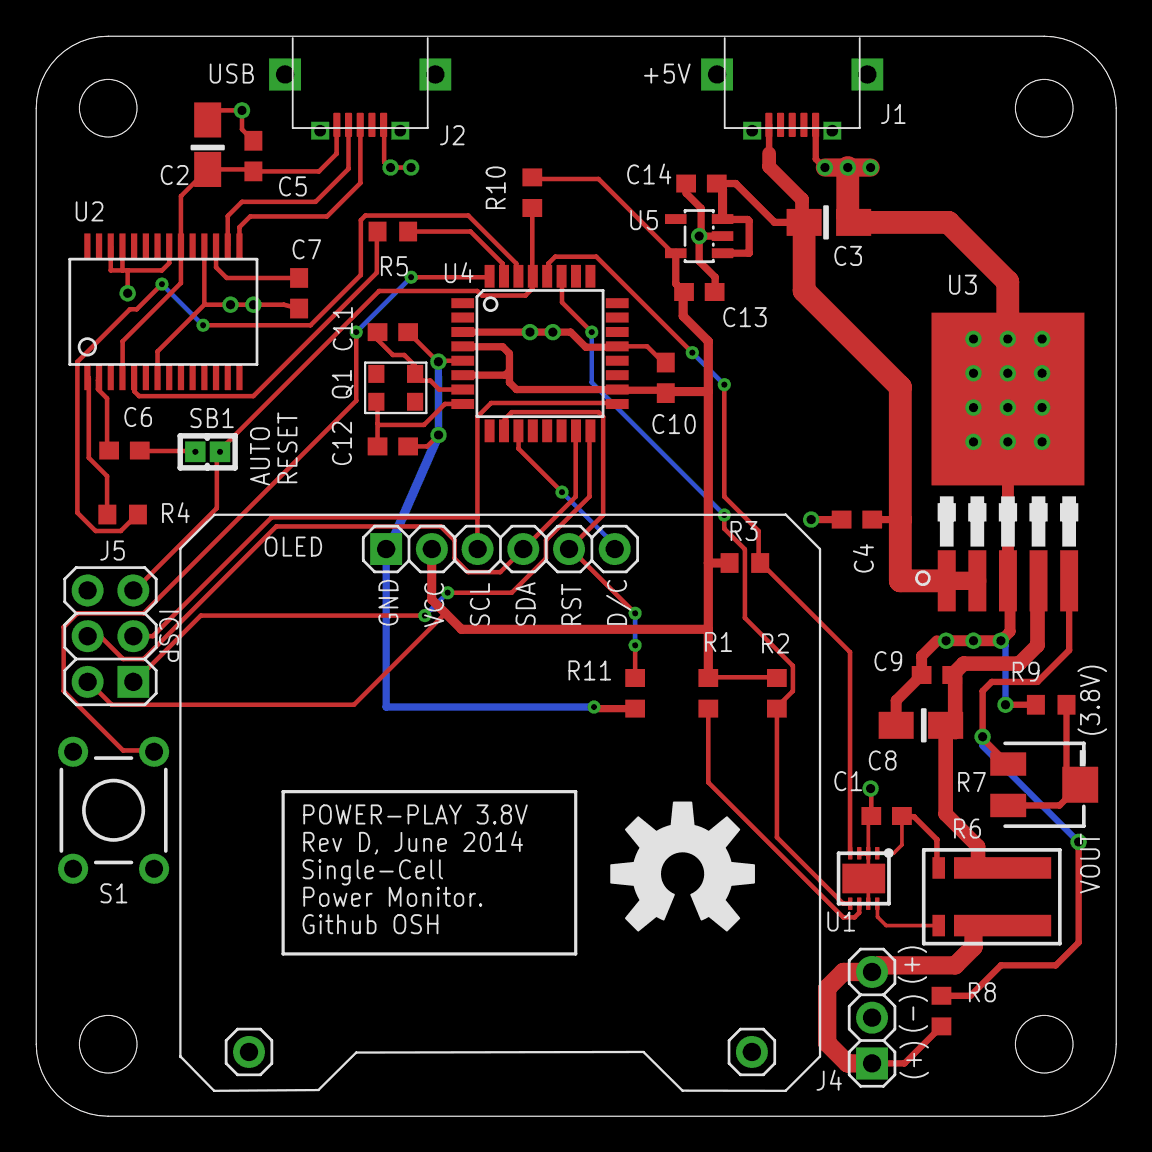
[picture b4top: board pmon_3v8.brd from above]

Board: 2 copper layers, 60.0 x 60.0 mm, 39 parts (0 on the bottom side), 31 nets.

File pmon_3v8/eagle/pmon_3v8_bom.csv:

Quantity,Description,Part Designators,Digikey Part Number,Comments
1,0.025 ohm 1% Kelvin,R6,FC4L64R025FERCT-ND,Ohmite FC4L64R025FER
5,3.3K 1% 1/10W 0603,R1  R2  R3  R9  R11,P3.30KHCT-ND,
1,8.2K 1% 1/10W 0603,R8,P8.20KHCT-ND,
3,10k 5% 1/10W 0603,R4  R5  R10,311-10KGRCT-ND,
1,1K 12 turns  side adjustment,R7,3224J-102ECT-ND,Bourns 3224J-1-102E
2,20pF 50V 5% 0603,C11  C12,311-1424-1-ND,
6,0.1uf 10% 25V 0603,C4  C5  C6  C7  C9  C10,311-1344-1-ND,Reduce C7 if interferes with ICSP reset (e.g. to 0.01)
3,Ceramic cap 1uF 16V 5% 0603,C1  C13  C14,445-1604-1-ND,
3,Tantalum cap 10uF 10%  16V 1206,C2  C3  C8,399-3684-1-ND,
1,"Heltec 1.3"" SPI 128X64 OLED WHITE monochrome display with RST pin.",OLED,,"http://www.heltec.diytrade.comor http://r.ebay.com/bVQ2CYMust have SSD1306 controller and these 6 pins: GND  VCC  SCL  SDA  RST  D/C (picture here  http://i.imgur.com/y3cWazS.jpg).  Manufacturer is http://www.heltec.cn. Heltec also similar blue models (with sh1063 controller) and 'new' models with different 6 pins (VCC and GND swapped  no RST pin)  these two models are incompatible with the current POWER PLAY design."
1,16Mhz crystal,Q1,CTX732CT-ND,CTS 403 Series  20pF.
1,ATMEGA328P TQFP32,U4,ATMEGA328P-AURCT-ND,Atmel AVR328P
1,FT232RL  SSOP28,U2,768-1007-1-ND,
1,LTC2943  DFN8,U1,LTC2943CDD#PBF-ND,
1,LT1764AEQ TO263,U3,LT1764AEQ#TRPBFCT-ND,Adjustable LDO 3A.
1,TC1015 SOT23-5,U5,TC10154.0VCT713CT-ND,Fixed LDO 4.0V.
1,Push button,S1,P12197S-ND        ,Panasonic EVQ-PAG09K
1,"3 positions  0.1"" header  straight",J4,S1011E-36-ND,Generic part. Height above board should be at most 8.5mm. The part number here is for a 36 position breakable strip so it can be used for multiple boards.
2,"1 position  0.1"" header straight",OLED mechanical support.,S1011E-36-ND,Generic part. Height above board should be at most 8.5mm. The part number here is for a 36 position breakable strip so it can be used for multiple boards.
1,RC Hitech/JR servo 3 positions male connector + 2 pins,Mates with J3,,Any RC store or ebay. The top cover laser cut was design for JR/Hitech housings  not Futaba.
2,Micro USB 'reversed' connector,J1 J2,H11611CT-ND,Hirose ZX62RD-AB-5P8.  Make sure it is a 'reversed' connector  otherwise the signals will be in reversed order.
1,PCB,,,Order the PCB from your favorite PCB manufacturer (2 layers  60x60mm).  Make sure to order a SMD stencil  preferably 5mil stainless steal but even a 5 mil stencil from oshstencils.com should work.
1,Top cover custom acrylic,,,"Laser cut fluorescent green 1/8"" acryilic."
1,Bottom cover custom acrylic,,,"Laser cut fluorescent green 1/8"" acryilic."
4,M3x6mm  pan head  philips machine screw,,335-1156-ND,Top cover screws
4,M3x10mm  pan head  philips machine screw,,335-1148-ND,Bottom cover screws
4,M3x6mm  round  threaded  female/female metal standoff,,952-1515-ND        ,Top cover standoff
4,M3x3mm round  non threaded nylon or metal spacer,,952-1526-ND,Bottom cover spacer

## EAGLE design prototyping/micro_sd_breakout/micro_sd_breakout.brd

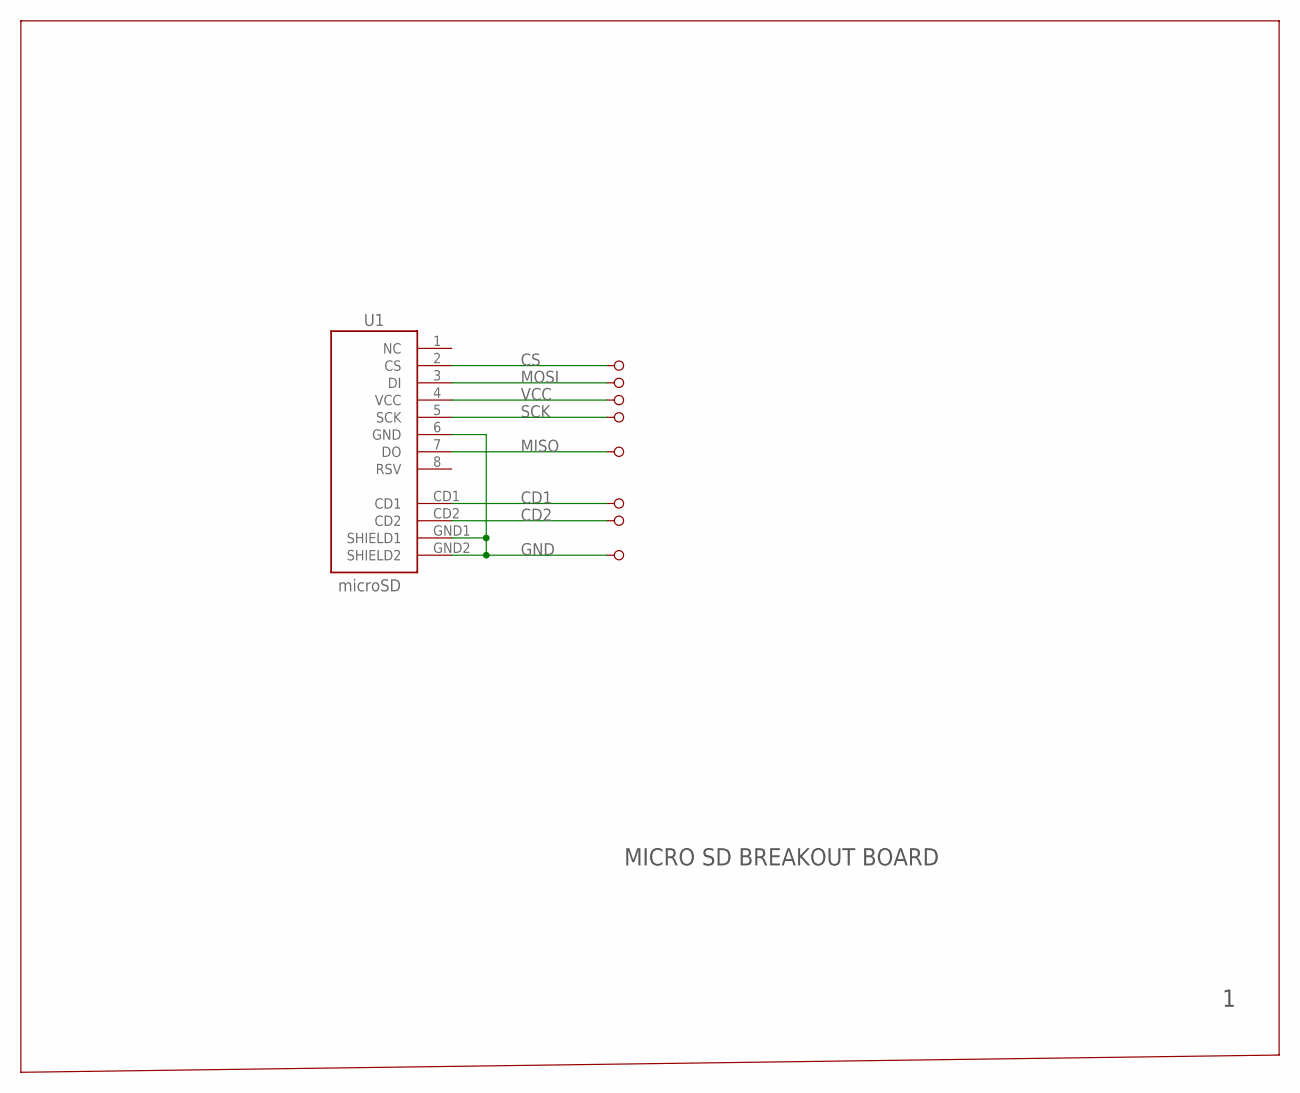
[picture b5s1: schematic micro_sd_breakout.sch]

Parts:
JP1, JP2, JP3, JP4, JP5, JP6, JP7, JP8: PINHD-1X1; 1X01
U1: microSD; MICRO-SD-SOCKET-PP

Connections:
CD1: JP6.1, U1.CD1
CD2: JP7.1, U1.CD2
CS: JP1.1, U1.2 (CS)
GND: JP8.1, U1.6 (GND), U1.GND1 (SHIELD1), U1.GND2 (SHIELD2)
MISO: JP5.1, U1.7 (DO)
MOSI: JP2.1, U1.3 (DI)
SCK: JP4.1, U1.5 (SCK)
VCC: JP3.1, U1.4 (VCC)

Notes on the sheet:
MICRO SD BREAKOUT BOARD

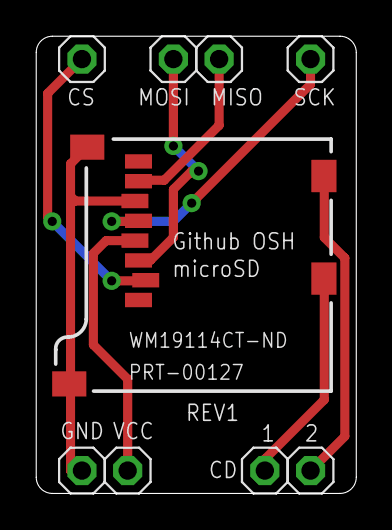
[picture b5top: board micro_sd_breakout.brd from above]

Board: 2 copper layers, 17.8 x 25.4 mm, 9 parts (0 on the bottom side), 8 nets.
